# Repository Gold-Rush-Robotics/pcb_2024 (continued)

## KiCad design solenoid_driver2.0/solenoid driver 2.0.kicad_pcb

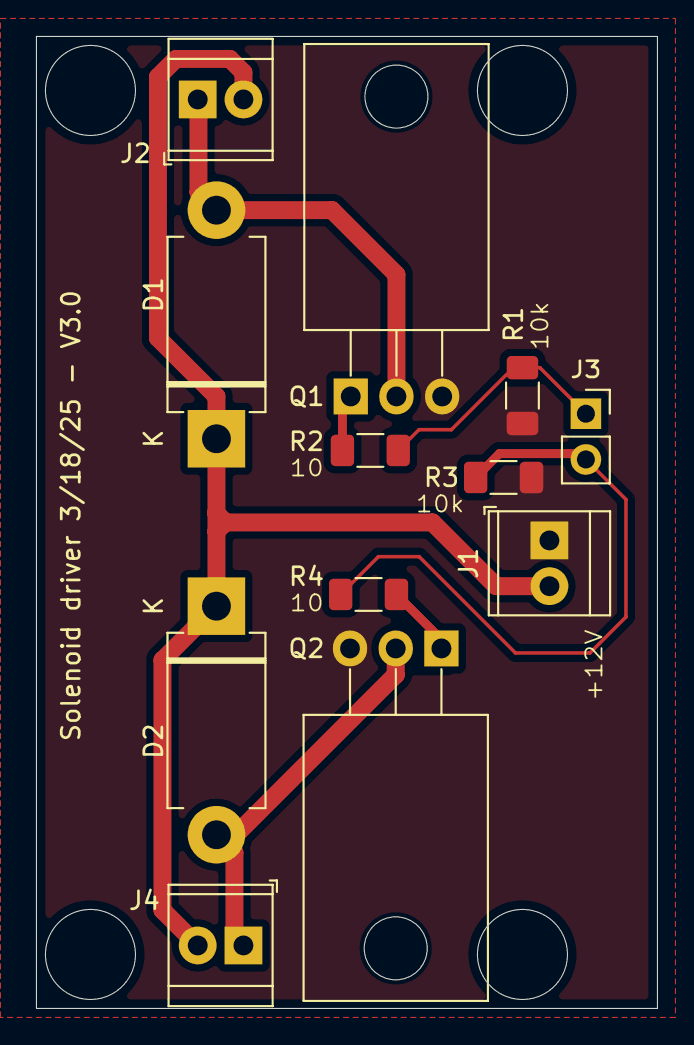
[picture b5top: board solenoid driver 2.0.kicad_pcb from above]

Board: 2 copper layers, 34.5 x 54.0 mm, 12 parts (0 on the bottom side), 8 nets.

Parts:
D1, D2: D; D_DO-201AD_P12.70mm_Horizontal
J1: 12v and gnd; TerminalBlock_TE_282834-2_1x02_P2.54mm_Horizontal
J2: solenoid1 screw terminal; TerminalBlock_TE_282834-2_1x02_P2.54mm_Horizontal
J3: signal 1 and 2; PinSocket_1x02_P2.54mm_Vertical
J4: solenoid2 screw terminal; TerminalBlock_TE_282834-2_1x02_P2.54mm_Horizontal
Q1, Q2: IRF3205; TO-220-3_Horizontal_TabDown
R1, R3: 10K; R_1206_3216Metric_Pad1.30x1.75mm_HandSolder
R2, R4: 10; R_1206_3216Metric_Pad1.30x1.75mm_HandSolder

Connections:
+12V: D1.1 (K), D2.1 (K), J1.2, J2.2, J4.2
GND: J1.1, Q1.3 (S), Q2.3 (S), R1.2, R3.2
drain1: D1.2 (A), J2.1, Q1.2 (D)
drain2: D2.2 (A), J4.1, Q2.2 (D)
pin1: J3.1, R1.1, R2.1
pin2: J3.2, R3.1, R4.1
r2 to gate1: Q1.1 (G), R2.2
r4 to gate2: Q2.1 (G), R4.2

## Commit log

2024-04-10 Made folders
2024-04-10 Added folders
2024-04-10 Created kiCad projects
2024-04-10 create resource folders
2024-04-10 Testing symbols
2024-04-15 Added IMC404 (roboclaw) symbol and footprint
2024-04-24 Modified main board to have SPICE simulation for reverse protection, updated projects to be on kicad 8
2024-05-05 added 3d model
2024-05-05 Added Symbols and footprints
2024-05-05 worked on swerve drive train board
2024-05-06 simplify schematic
2024-05-06 add rgb led
2024-05-06 added footprints to everything + other updates
2024-05-06 removed un needed pages
2024-05-06 first layout pass
2024-05-06 layout and routing for swerve
2024-05-11 Began adding power to the mainboard
2024-05-11 update schematic and make a blank pcb layout for testing
2024-05-18 Add can test board
2024-05-18 remove lock files
2024-05-18 Added reverse protection for 5v and 3.3v buck convertors
2024-05-18 Updated gitignore
2024-05-20 final thing we ordered
2024-05-20 work on the swerve drive
2024-05-29 switched motor drivers out schematic and footprint
2024-06-04 Various small things, such as 12v power connectors, jetson header, can stuff, and bypass resistors for reverse protection
2024-06-05 Added QWIIC Connectors for i2c, ethernet ports for attachment, updated XT style power connector counts, added i2c multiplexer
2024-06-07 work on fitting into footprint
2024-06-11 new outline
2024-06-12 finished first layout and routing pass
2024-06-12 cleaning
2024-06-12 Updated 12v to 5v chip to be the same as 3.3v, but with adjusted resistors
2024-06-13 finalize pcb
2024-06-13 Minor changes, renamed ethernet ports to attachment and adding warning
2024-07-20 Started laying out the board
2024-07-29 Changed connector for jetson, adjusted layout, used vertical ethernet
2024-07-30 did some rearangement, added 3d models that were missing
2024-08-16 Archived 3d models so they appear on everyones computer
2024-08-16 Updated schematic sheet to have proper name, date, orgnization, and note
2024-08-16 more notes
2024-08-16 updated capacitor value for can split termination
2024-08-20 update can test to teensy 41
2024-08-21 make fixes sylvester reccomended
2024-08-21 cleanup pcb
2024-08-21 cleanup schematic
2024-09-20 Added mainboard step
2024-09-20 Fixed certain 3d models not showing
2024-09-20 Moved barrel jack forward a bit
2024-10-11 layed out mainboard as tano reccomended, added mounting holes, images, and new step file
2024-10-11 removed 3 of the can ports, re-layed out the buck converters, exported new step
2024-10-11 added a .wrl of the mainboard
2024-10-12 added labels, moved a few items
2024-10-13 Routed board, created gerbers
2024-10-13 adjusted gap between rj45 ports
2024-10-16 Fixed error with PNP mosfet
2024-10-16 Moved can_test board up 1
2024-10-16 Fixed path for footprints
2024-10-17 Created a version of the mainboard with XT30 and 2 pin QWIIC for data output
2024-10-17 Added 3d models
2024-10-17 Fixed trace that had a unecessary via
2024-10-17 move extra XT30 to bottom
2024-10-17 Reviewed PCB with justin and made changes
2024-11-12 Started working on mechanum drive PCB
2024-11-13 Cleaned up schematic, added LDO regulator for 5v to mechanum board
2024-11-15 Added step for tano
2024-11-26 Added a 2nd pololu board
2024-11-26 Added step
2024-11-27 create symbol and footprint for the Pololu 18v17 motor controller
2024-11-27 create symbol and footprint for the Pololu 18v17 motor controller (#4)
2025-01-04 Added render
2025-01-15 Added connectors for motos, added schematic
2025-01-15 Updated schematic, started new layout of board
2025-01-15 Added cs2
2025-01-15 add 3d model for second motor driver
2025-01-17 Updated board size and layout
2025-01-18 started routing
2025-01-19 revise Teensy footprint, first pass at routing
2025-01-20 Updated routing, added labels
2025-01-20 Updated routing, created images, created gerbers
2025-01-20 fixed pullup
2025-01-20 neaten up stitching vias
2025-01-21 Updated gerbers, added step
2025-03-31 move solenoid into its own folder
2025-04-06 updates to manufacture
2025-04-08 produced
